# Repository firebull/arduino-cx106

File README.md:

# arduino-cx106
Цифровой аналог механического счётчика СХ-106

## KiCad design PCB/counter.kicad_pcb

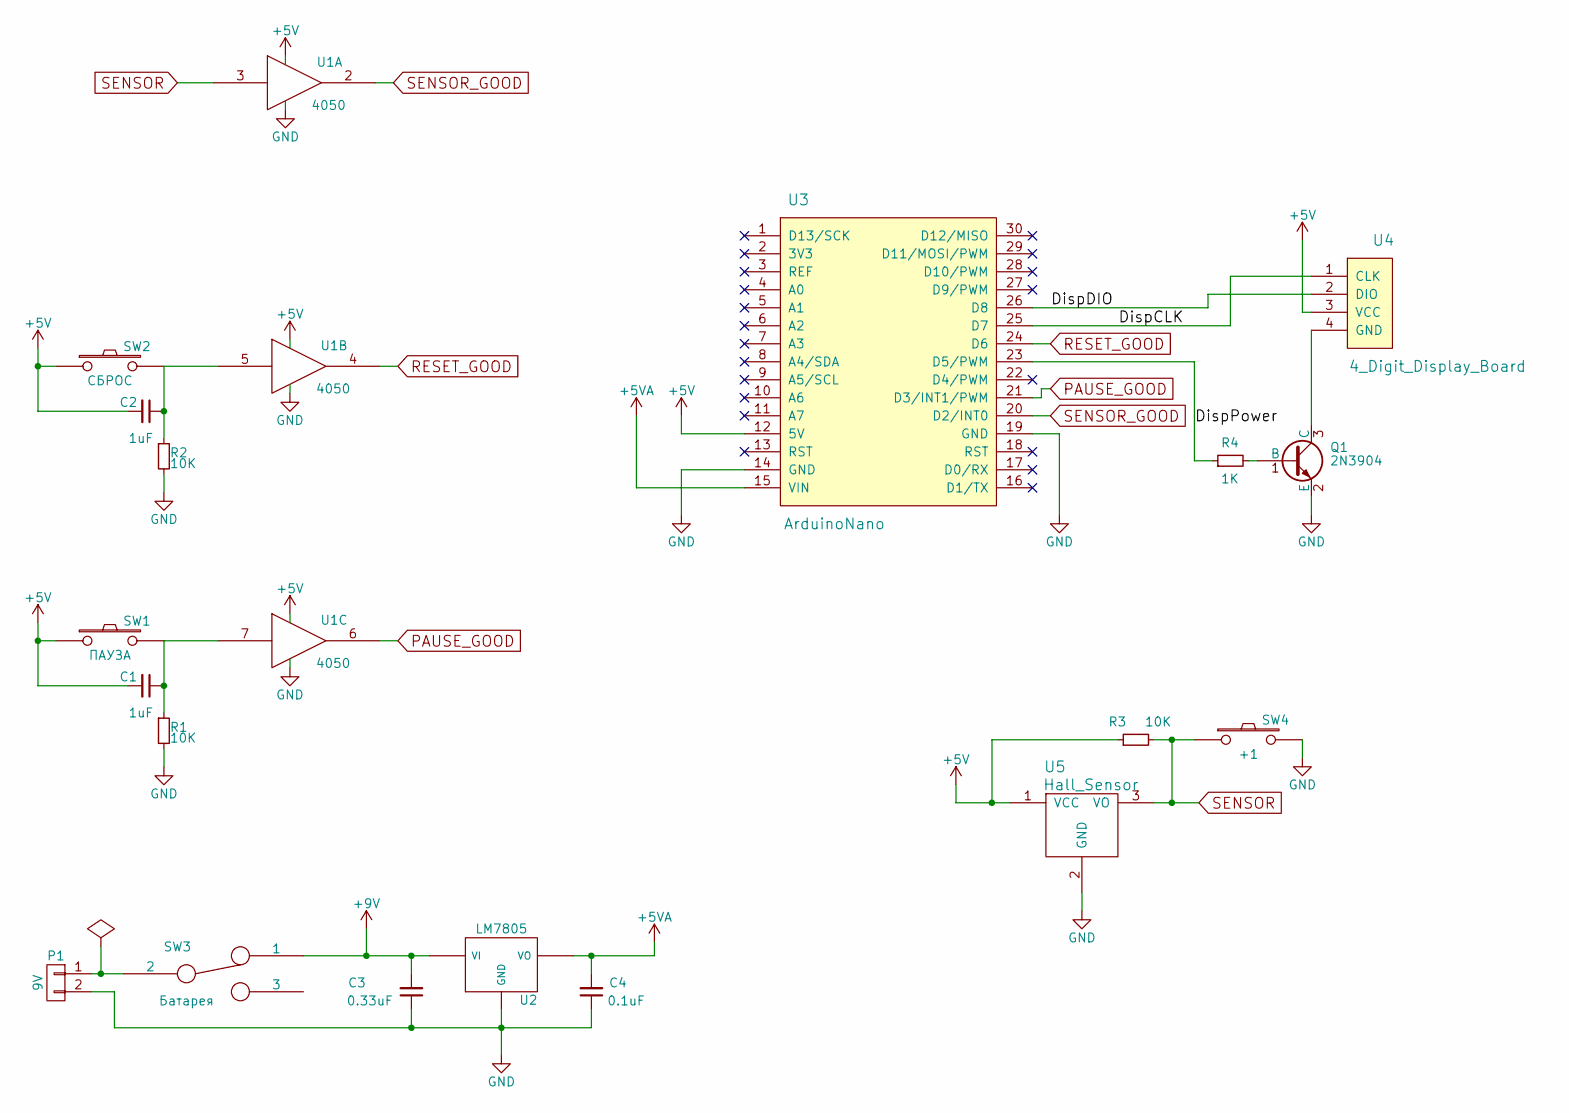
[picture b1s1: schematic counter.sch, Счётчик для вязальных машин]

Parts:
C1, C2: 1uF; C_1206_HandSoldering
C3: 0.33uF; C_1206_HandSoldering
C4: 0.1uF; C_1206_HandSoldering
P1: 9V; Pin_Header_Angled_1x02
Q1: 2N3904; TO-92_Inline_Narrow_Oval
R1, R2, R3: 10K; R_1206_HandSoldering
R4: 1K; R_1206_HandSoldering
SW1: ПАУЗА; Tactile_SW_PUSH-12mm_with_Cap_white
SW2: СБРОС; Tactile_SW_PUSH-12mm_with_Cap_white
SW3: Батарея; SW_PUSH_x2
SW4: +1; Btn_Tack_5mm
U1: 4050; DIP-16_W7.62mm
U2: LM7805; LM7805_TO-220_Neutral123_Horizontal_LargePads_with_GND_pad
U3: ArduinoNano; ArduinoNanoUpper
U4: 4_Digit_Display_Board; 4-digit-display-board
U5: Hall_Sensor; Hall_Sensor_A314x

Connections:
+5V: C1.2, C2.2, R3.1, SW1.1, SW2.1, U1.1 (VCC), U3.12 (5V), U4.3 (VCC), U5.1 (VCC)
+5VA: C4.2, U2.3 (VO), U3.15 (VIN)
+9V: C3.2, SW3.1, U2.1 (VI)
/DispCLK: U3.25 (D7), U4.1 (CLK)
/DispDIO: U3.26 (D8), U4.2 (DIO)
/DispPower: R4.1, U3.23 (D5/PWM)
GND: C3.1, C4.1, P1.2, Q1.2 (E), R1.2, R2.2, SW4.2, U1.8 (VSS), U2.2 (GND), U3.14 (GND), U3.19 (GND), U5.2 (GND)
unnamed: C1.1, R1.1, SW1.2, U1.7
unnamed: C2.1, R2.1, SW2.2, U1.5
unnamed: P1.1, SW3.2
unnamed: Q1.1 (B), R4.2
unnamed: Q1.3 (C), U4.4 (GND)
PAUSE_GOOD: U1.6, U3.21 (D3/INT1/PWM)
RESET_GOOD: U1.4, U3.24 (D6)
SENSOR: R3.2, SW4.1, U1.3, U5.3 (VO)
SENSOR_GOOD: U1.2, U3.20 (D2/INT0)

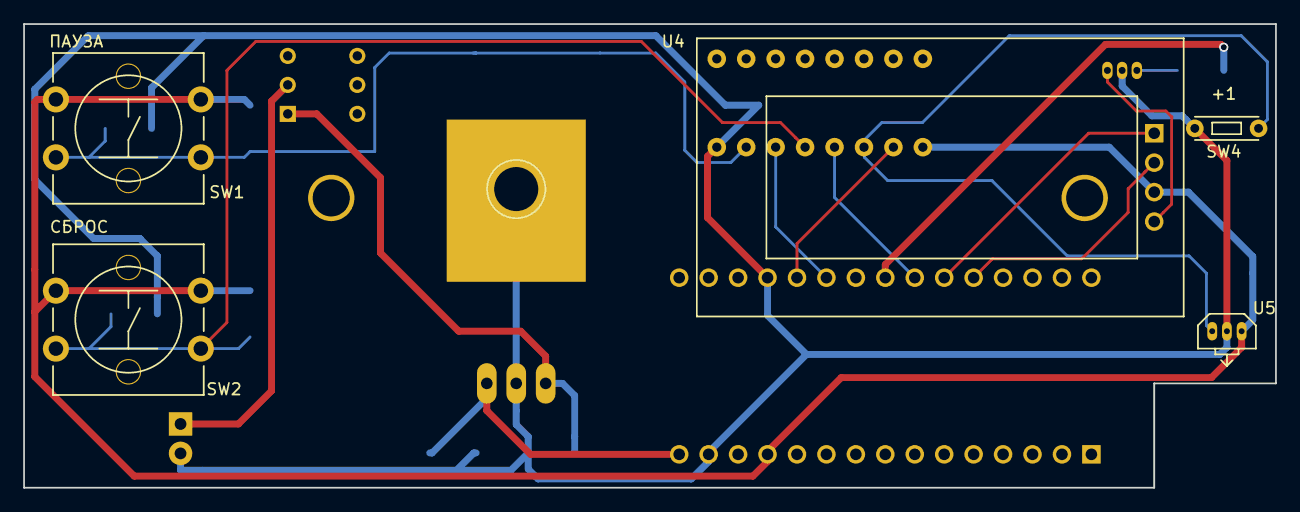
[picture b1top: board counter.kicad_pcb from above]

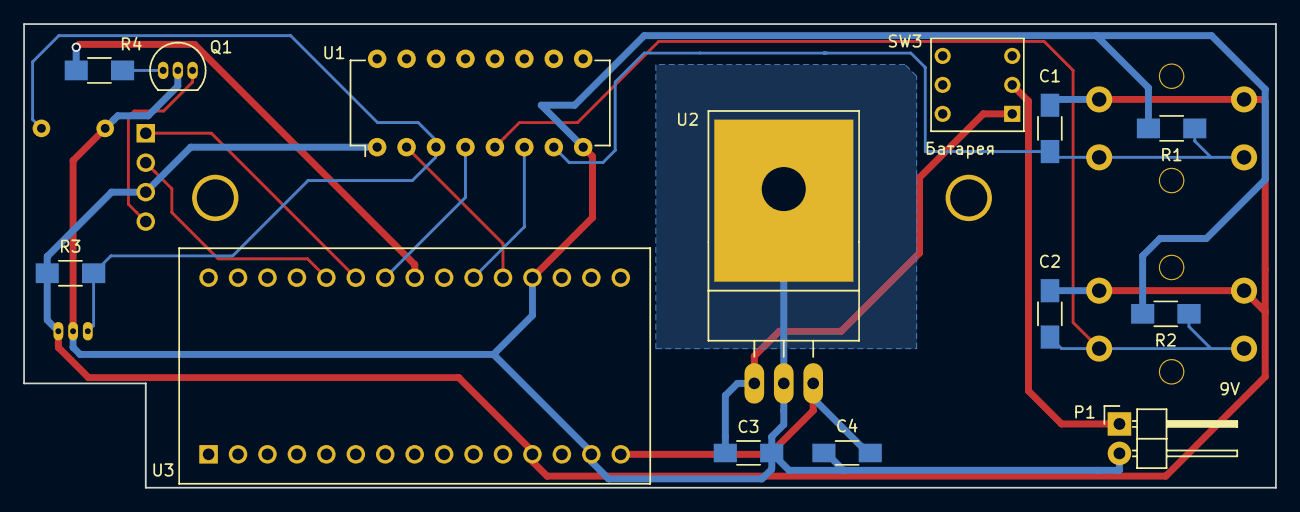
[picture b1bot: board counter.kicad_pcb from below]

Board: 2 copper layers, 108.0 x 40.0 mm, 19 parts (14 on the bottom side), 16 nets.

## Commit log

2016-03-15 Добавил наброски платы в KiCad и заготовку скетча
2016-03-15 Первое приближение разводки Добавил выключатель с фиксатором на батарейку
2016-03-17 Добавил инкрементальную кнопку
